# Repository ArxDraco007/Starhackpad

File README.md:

# Starhackpad

## Why did I do this project?
If you use a computer, tablet, or phone (I don't know what you are using otherwise). A macropad is one of the best add-ons you can have to increase your productivity. A macropad is a small, compact, secondary keypad with fully programmable keys. It allows you to execute complex keyboard shortcuts, automate repetitive tasks, or launch applications with a single press of a button. One press of a button can run the commands to curse at your friends when they are playing like they usually would.

NOW FOR SOME...
## PICTURES!!! 

BOM! - 
## Kit Items

| Item | Description | Quantity | Unit Price ($) | Total Price ($) | Link |
|------|-------------|----------|----------------|-----------------|------|
| SEEED Studios XIAO RP2040 | Microcontroller | 1 | 6.57 | 6.57 | https://robu.in/product/seeed-studio-xiao-rp2040-v1-0/ |
| Cherry MX Switches | Switches | 10 | 0.399 | 3.99 | https://meckeys.com/shop/accessories/keyboard-accessories/key-switches/cherry-mx-rgb-switch/ |
| Blank Cherry MX-Style Keycaps | Keycaps | 5 | 0.212 | 1.06 | https://meckeys.com/shop/accessories/keyboard-accessories/keycaps/blank-dsa-keycaps-1u/ |
| Alps EC-11 Rotary Encoder | Knob | 1 | 1.28 | 1.28 | https://roboticsdna.in/product/rotary-encoder-module-for-arduino-brick-sensor-development-round-audio-rotating-potentiometer-knob-cap-ec11/ |
| M3x16mm Screws | Case Screws | 1 | 2.99 | 2.99 | https://www.amazon.in/Immech-Socket-Stainless-Machine-Quantity/dp/B07XYRXMML |
| M3x5x4mm Heat-Set Inserts | Case Screw Inserts | 1 | 0.95 | 0.95 | https://robu.in/product/m3-x-4-mm-brass-heat-set-knurl-threaded-round-insert-nut-25-pcs/ |
**Final Price for Kit Items: $16.84**
Case Items
| Item | Description | Quantity | Unit Price ($) | Total Price ($) | Link |
| 3D-printed Case (Self-Provided) | Approx. 156g PLA | 1 | 0 | 0 | — |
| LionCircuits PCB for Hackpad | PCB (MOQ 5) | 5 | 1.80 | 9.00 | https://order.lioncircuits.com/projectdetails/212426/quotation |
Final Price for Case Items: $9
Grand Total
| Category | Cost ($) |
| Kit Items | 16.84 |
| Case Items | 9 |
| **Grand Total** | **25.60** |

Tutorial - https://hackpad.hackclub.com/

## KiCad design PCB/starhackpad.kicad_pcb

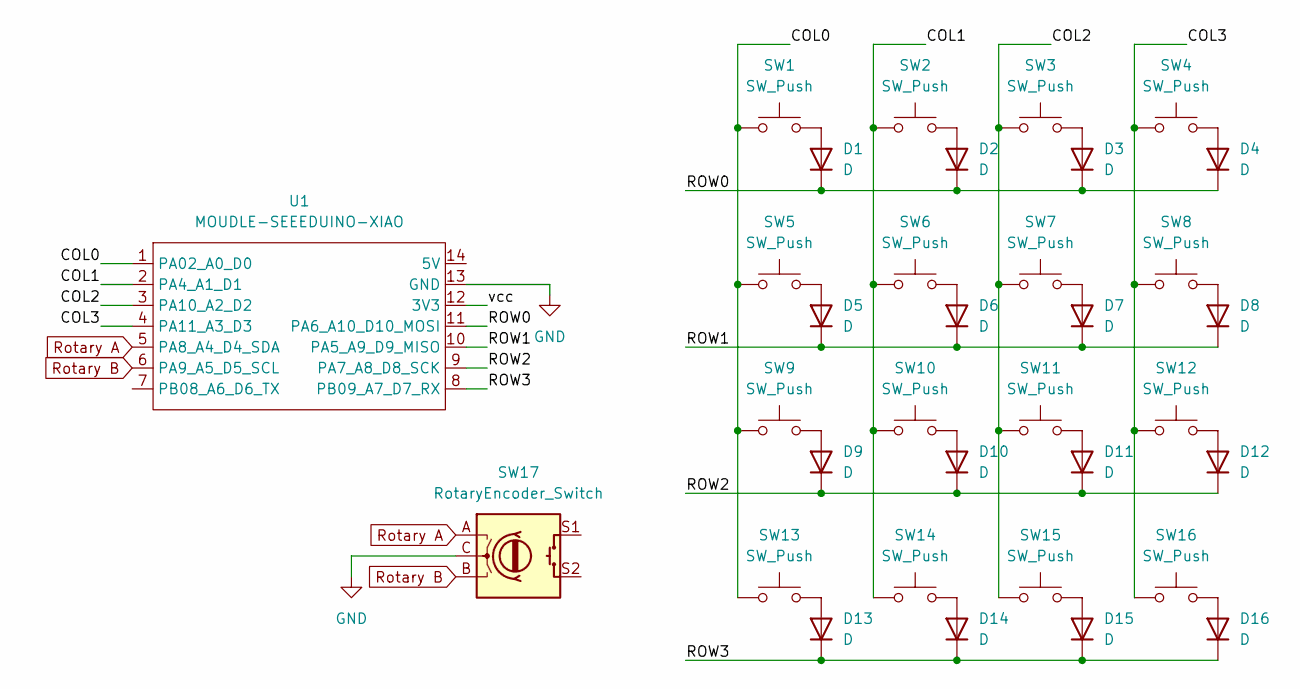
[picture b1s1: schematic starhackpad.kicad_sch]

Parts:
D1, D2, D3, D4, D5, D6, D7, D8, D9, D10, D11, D12, D13, D14, D15, D16: D; D_SOD-123
SW1, SW2, SW3, SW4, SW5, SW6, SW7, SW8, SW9, SW10, SW11, SW12, SW13, SW14, SW15, SW16: SW_Push; SW_Cherry_MX_1.00u_PCB
SW17: RotaryEncoder_Switch; RotaryEncoder_Alps_EC11E-Switch_Vertical_H20mm
U1: MOUDLE-SEEEDUINO-XIAO; XIAO-Generic-Hybrid-14P-2.54-21X17.8MM

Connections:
/COL0: SW1.1, SW5.1, SW9.1, SW13.1, U1.1 (PA02_A0_D0)
/COL1: SW2.1, SW6.1, SW10.1, SW14.1, U1.2 (PA4_A1_D1)
/COL2: SW3.1, SW7.1, SW11.1, SW15.1, U1.3 (PA10_A2_D2)
/COL3: SW4.1, SW8.1, SW12.1, SW16.1, U1.4 (PA11_A3_D3)
/ROW0: D1.1 (K), D2.1 (K), D3.1 (K), D4.1 (K), U1.11 (PA6_A10_D10_MOSI)
/ROW1: D5.1 (K), D6.1 (K), D7.1 (K), D8.1 (K), U1.10 (PA5_A9_D9_MISO)
/ROW2: D9.1 (K), D10.1 (K), D11.1 (K), D12.1 (K), U1.9 (PA7_A8_D8_SCK)
/ROW3: D13.1 (K), D14.1 (K), D15.1 (K), D16.1 (K), U1.8 (PB09_A7_D7_RX)
/vcc: U1.12 (3V3)
GND: SW17.C, U1.13 (GND)
unnamed: D1.2 (A), SW1.2
unnamed: D2.2 (A), SW2.2
unnamed: D3.2 (A), SW3.2
unnamed: D4.2 (A), SW4.2
unnamed: D5.2 (A), SW5.2
unnamed: D6.2 (A), SW6.2
unnamed: D7.2 (A), SW7.2
unnamed: D8.2 (A), SW8.2
unnamed: D9.2 (A), SW9.2
unnamed: D10.2 (A), SW10.2
unnamed: D11.2 (A), SW11.2
unnamed: D12.2 (A), SW12.2
unnamed: D13.2 (A), SW13.2
unnamed: D14.2 (A), SW14.2
unnamed: D15.2 (A), SW15.2
unnamed: D16.2 (A), SW16.2
Rotary A: SW17.A, U1.5 (PA8_A4_D4_SDA)
Rotary B: SW17.B, U1.6 (PA9_A5_D5_SCL)

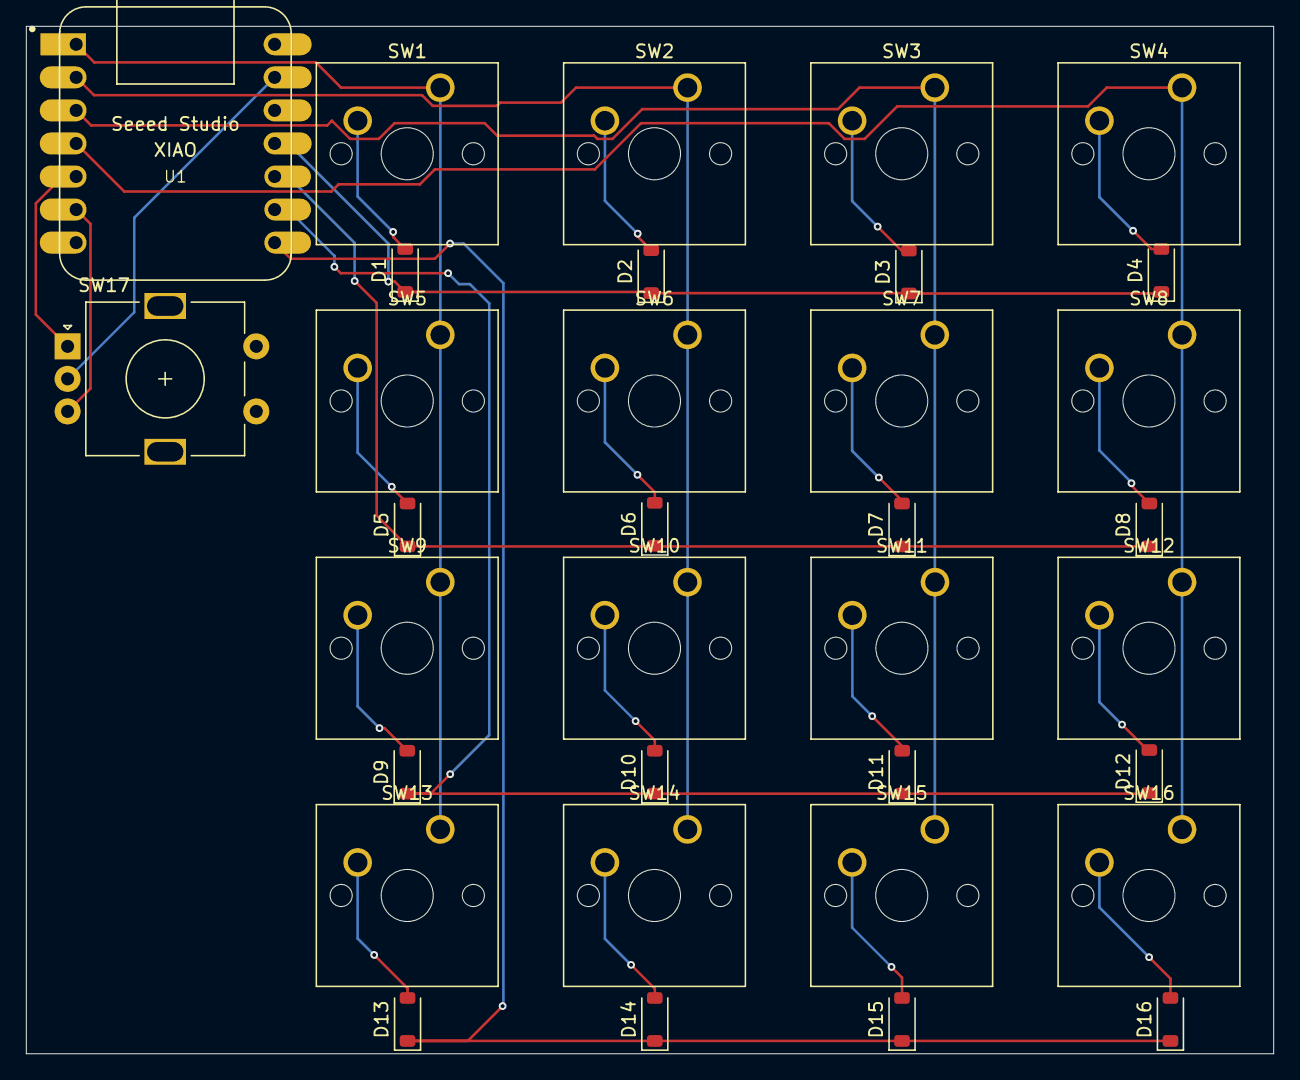
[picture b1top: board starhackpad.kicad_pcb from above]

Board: 2 copper layers, 95.8 x 78.9 mm, 34 parts (0 on the bottom side), 27 nets.

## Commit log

2026-06-09 cad and firmware
2026-06-09 production files
